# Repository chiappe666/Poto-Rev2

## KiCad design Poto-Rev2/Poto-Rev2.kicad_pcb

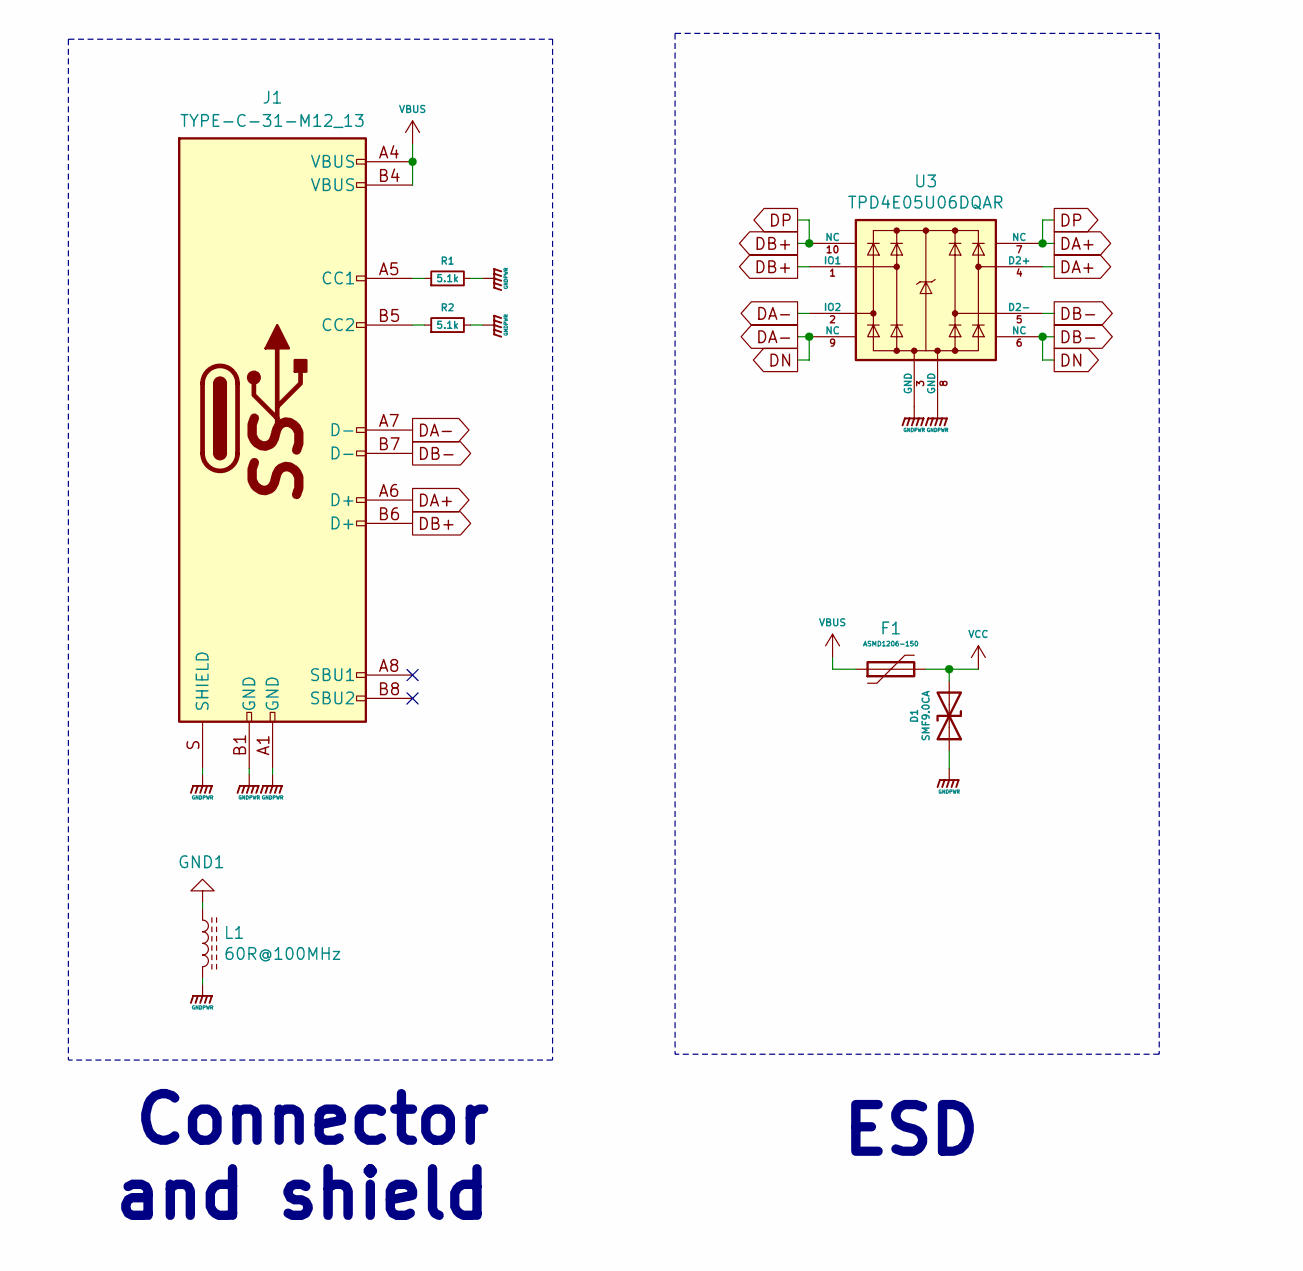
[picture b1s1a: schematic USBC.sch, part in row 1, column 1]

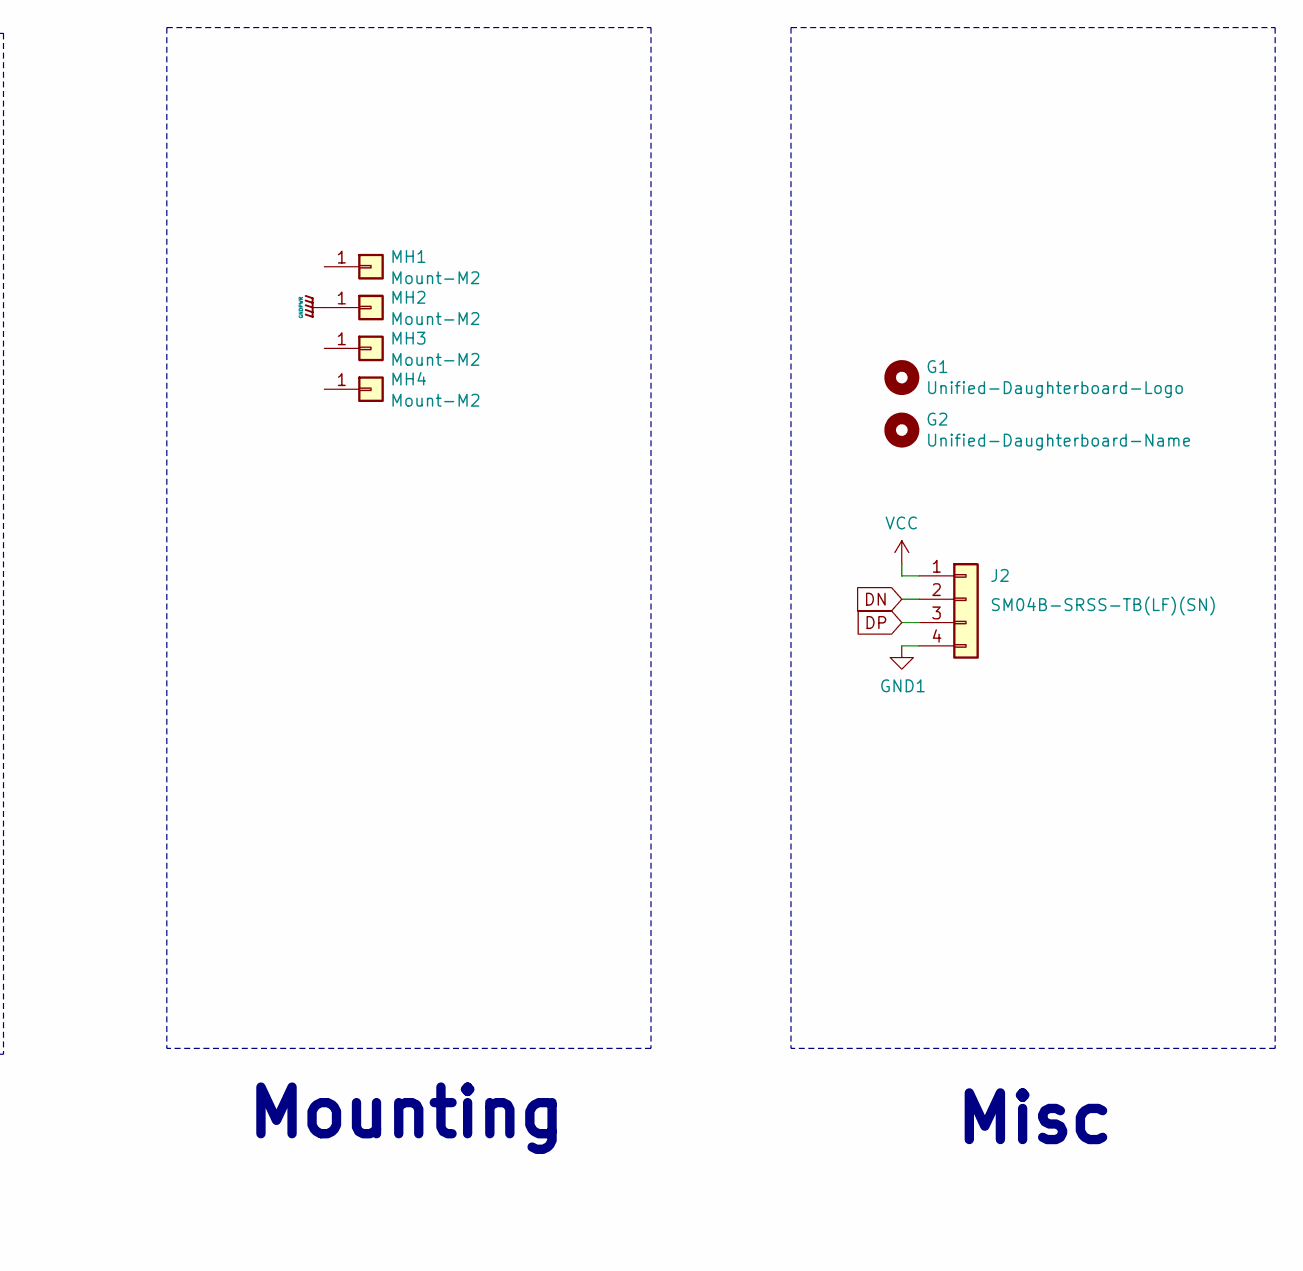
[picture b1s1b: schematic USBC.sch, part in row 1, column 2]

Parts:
D1: SMF9.0CA; D_SOD-123_Bidirectional; Manufacturer Part No SMF9.0CA; LCSC Part No C123799
F1: ASMD1206-150; Fuse_1206_3216Metric; Manufacturer Part No ASMD1206-150; LCSC Part No C135342
G1: Unified-Daughterboard-Logo; Unified-Daughterboard-Logo.pretty
G2: Unified-Daughterboard-Name; Unified-Daughterboard-Name.pretty
J1: TYPE-C-31-M12_13; TYPE-C-31-M-12; Manufacturer Part No TYPE-C-31-M-12; LCSC Part No C165948
J2: SM04B-SRSS-TB(LF)(SN); JST-SR-4; Manufacturer Part No SM04B-SRSS-TB(LF)(SN); LCSC Part No C160404
L1: 60R@100MHz; L_1206_3216Metric; Manufacturer Part No MLB3216-600P4A(f); LCSC Part No C33600
MH1, MH2, MH3, MH4: Mount-M2; Generic-Mounthole
R1, R2: 5.1k; R_0603_1608Metric; LCSC Part No C23186
U1: TPD4E05U06DQAR; USON-10_2.5x1.0mm_P0.5mm; Manufacturer Part No TPD4E05U06DQAR; LCSC Part No C138714

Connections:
GND1: J2.4, L1.1
unnamed: J1.A5 (CC1), R1.1
unnamed: J1.B5 (CC2), R2.1
VBUS: F1.1, J1.A4 (VBUS), J1.B4 (VBUS)
VCC: D1.2 (A2), F1.2, J2.1

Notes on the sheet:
Connector and shield
ESD
Mounting
Misc

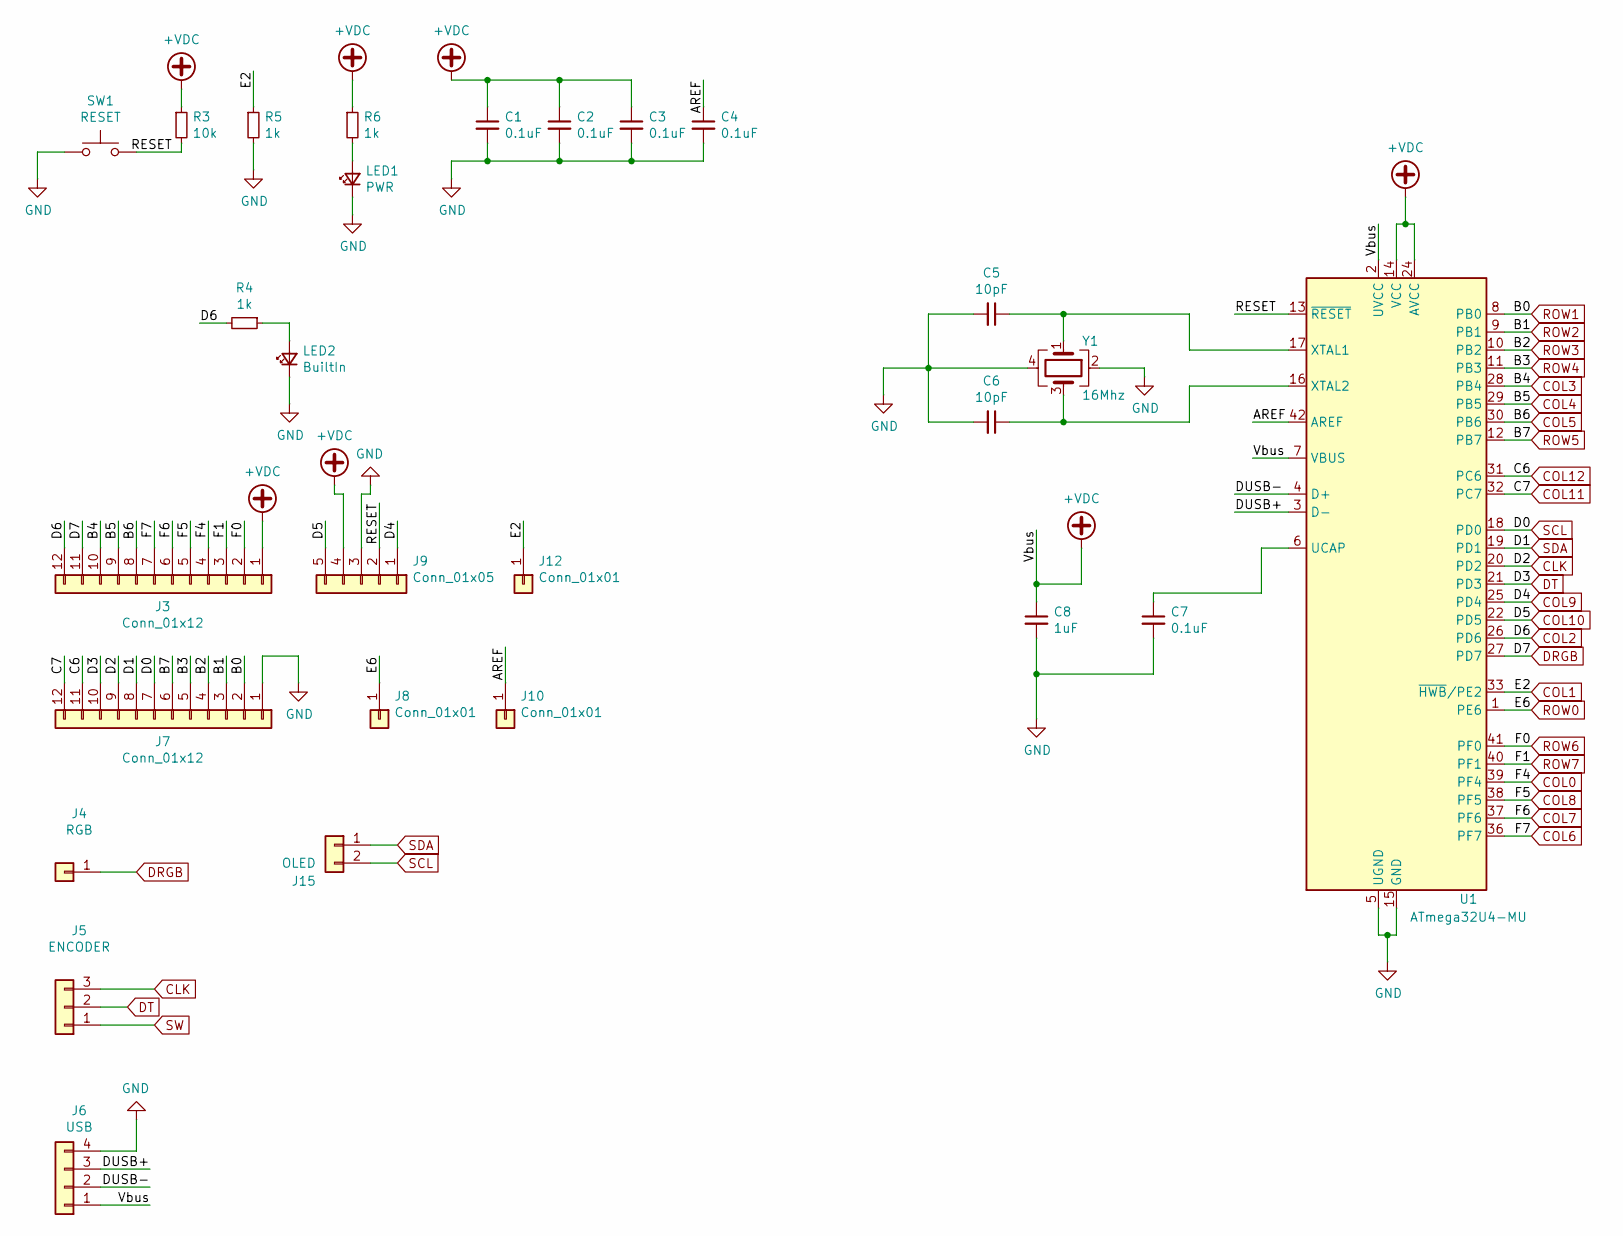
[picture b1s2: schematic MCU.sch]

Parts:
C1, C2, C3, C4, C7: 0.1uF; C_0402_1005Metric_Pad0.74x0.62mm_HandSolder; Manufacturer Part No CL05B104KO5NNNC; LCSC Part No C1525
C5, C6: 10pF; C_0402_1005Metric_Pad0.74x0.62mm_HandSolder; Manufacturer Part No CL05C100JB5NNNC; LCSC Part No C32949
C8: 1uF; C_0402_1005Metric_Pad0.74x0.62mm_HandSolder; Manufacturer Part No CL05A105KA5NQNC; LCSC Part No C52923
J3, J7: Conn_01x12; PinHeader_1x12_P2.54mm_Vertical
J4: RGB; PinHeader_1x01_P2.54mm_Vertical
J5: ENCODER; PinHeader_1x03_P2.54mm_Vertical
J6: USB; JST-SR-4
J8, J10: Conn_01x01; PinHeader_1x01_P2.54mm_Vertical
J9: Conn_01x05; PinHeader_1x05_P2.54mm_Vertical
J12: Conn_01x01; PinHeader_1x01_P1.00mm_Vertical
J15: OLED; PinHeader_1x02_P2.54mm_Vertical
LED1: PWR; LED_0603_1608Metric_Pad1.05x0.95mm_HandSolder
LED2: BuiltIn; LED_0603_1608Metric_Pad1.05x0.95mm_HandSolder
R3: 10k; R_0603_1608Metric_Pad0.98x0.95mm_HandSolder
R4, R5, R6: 1k; R_0603_1608Metric_Pad0.98x0.95mm_HandSolder
SW1: RESET; K2-1187SQ-A4SW-06
U1: ATmega32U4-MU; QFN-44-1EP_7x7mm_P0.5mm_EP5.2x5.2mm
Y1: 16Mhz; Crystal_SMD_3225-4Pin_3.2x2.5mm_HandSoldering

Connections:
/MCU/AREF: C4.1, J10.1, U1.42 (AREF)
/MCU/RESET: J9.2, R3.2, SW1.2, U1.13 (~RESET)
CLK: J5.3, J7.9, U1.20 (PD2)
COL0: J3.4, U1.39 (PF4); also elsewhere on the board
COL1: J12.1, R5.1, U1.33 (~HWB~/PE2); also elsewhere on the board
COL2: J3.12, R4.2, U1.26 (PD6); also elsewhere on the board
COL3: J3.10, U1.28 (PB4); also elsewhere on the board
COL4: J3.9, U1.29 (PB5); also elsewhere on the board
COL5: J3.8, U1.30 (PB6); also elsewhere on the board
COL6: J3.7, U1.36 (PF7); also elsewhere on the board
COL7: J3.6, U1.37 (PF6); also elsewhere on the board
COL8: J3.5, U1.38 (PF5); also elsewhere on the board
COL9: J9.1, U1.25 (PD4); also elsewhere on the board
COL10: J9.5, U1.22 (PD5); also elsewhere on the board
COL11: J7.12, U1.32 (PC7); also elsewhere on the board
COL12: J7.11, U1.31 (PC6); also elsewhere on the board
DRGB: J3.11, J4.1, U1.27 (PD7)
DT: J5.2, J7.10, U1.21 (PD3)
unnamed: C5.1, U1.17 (XTAL1), Y1.1
unnamed: C6.1, U1.16 (XTAL2), Y1.3
unnamed 127: LED1.2 (A), R6.2; also elsewhere on the board
unnamed 128: LED2.2 (A), R4.1; also elsewhere on the board
ROW4: J7.5, U1.11 (PB3); also elsewhere on the board
ROW5: J7.6, U1.12 (PB7); also elsewhere on the board
ROW6: J3.2, U1.41 (PF0); also elsewhere on the board
ROW7: J3.3, U1.40 (PF1); also elsewhere on the board
SCL: J7.7, J15.2, U1.18 (PD0)
SDA: J7.8, J15.1, U1.19 (PD1)
SW: J5.1; also elsewhere on the board

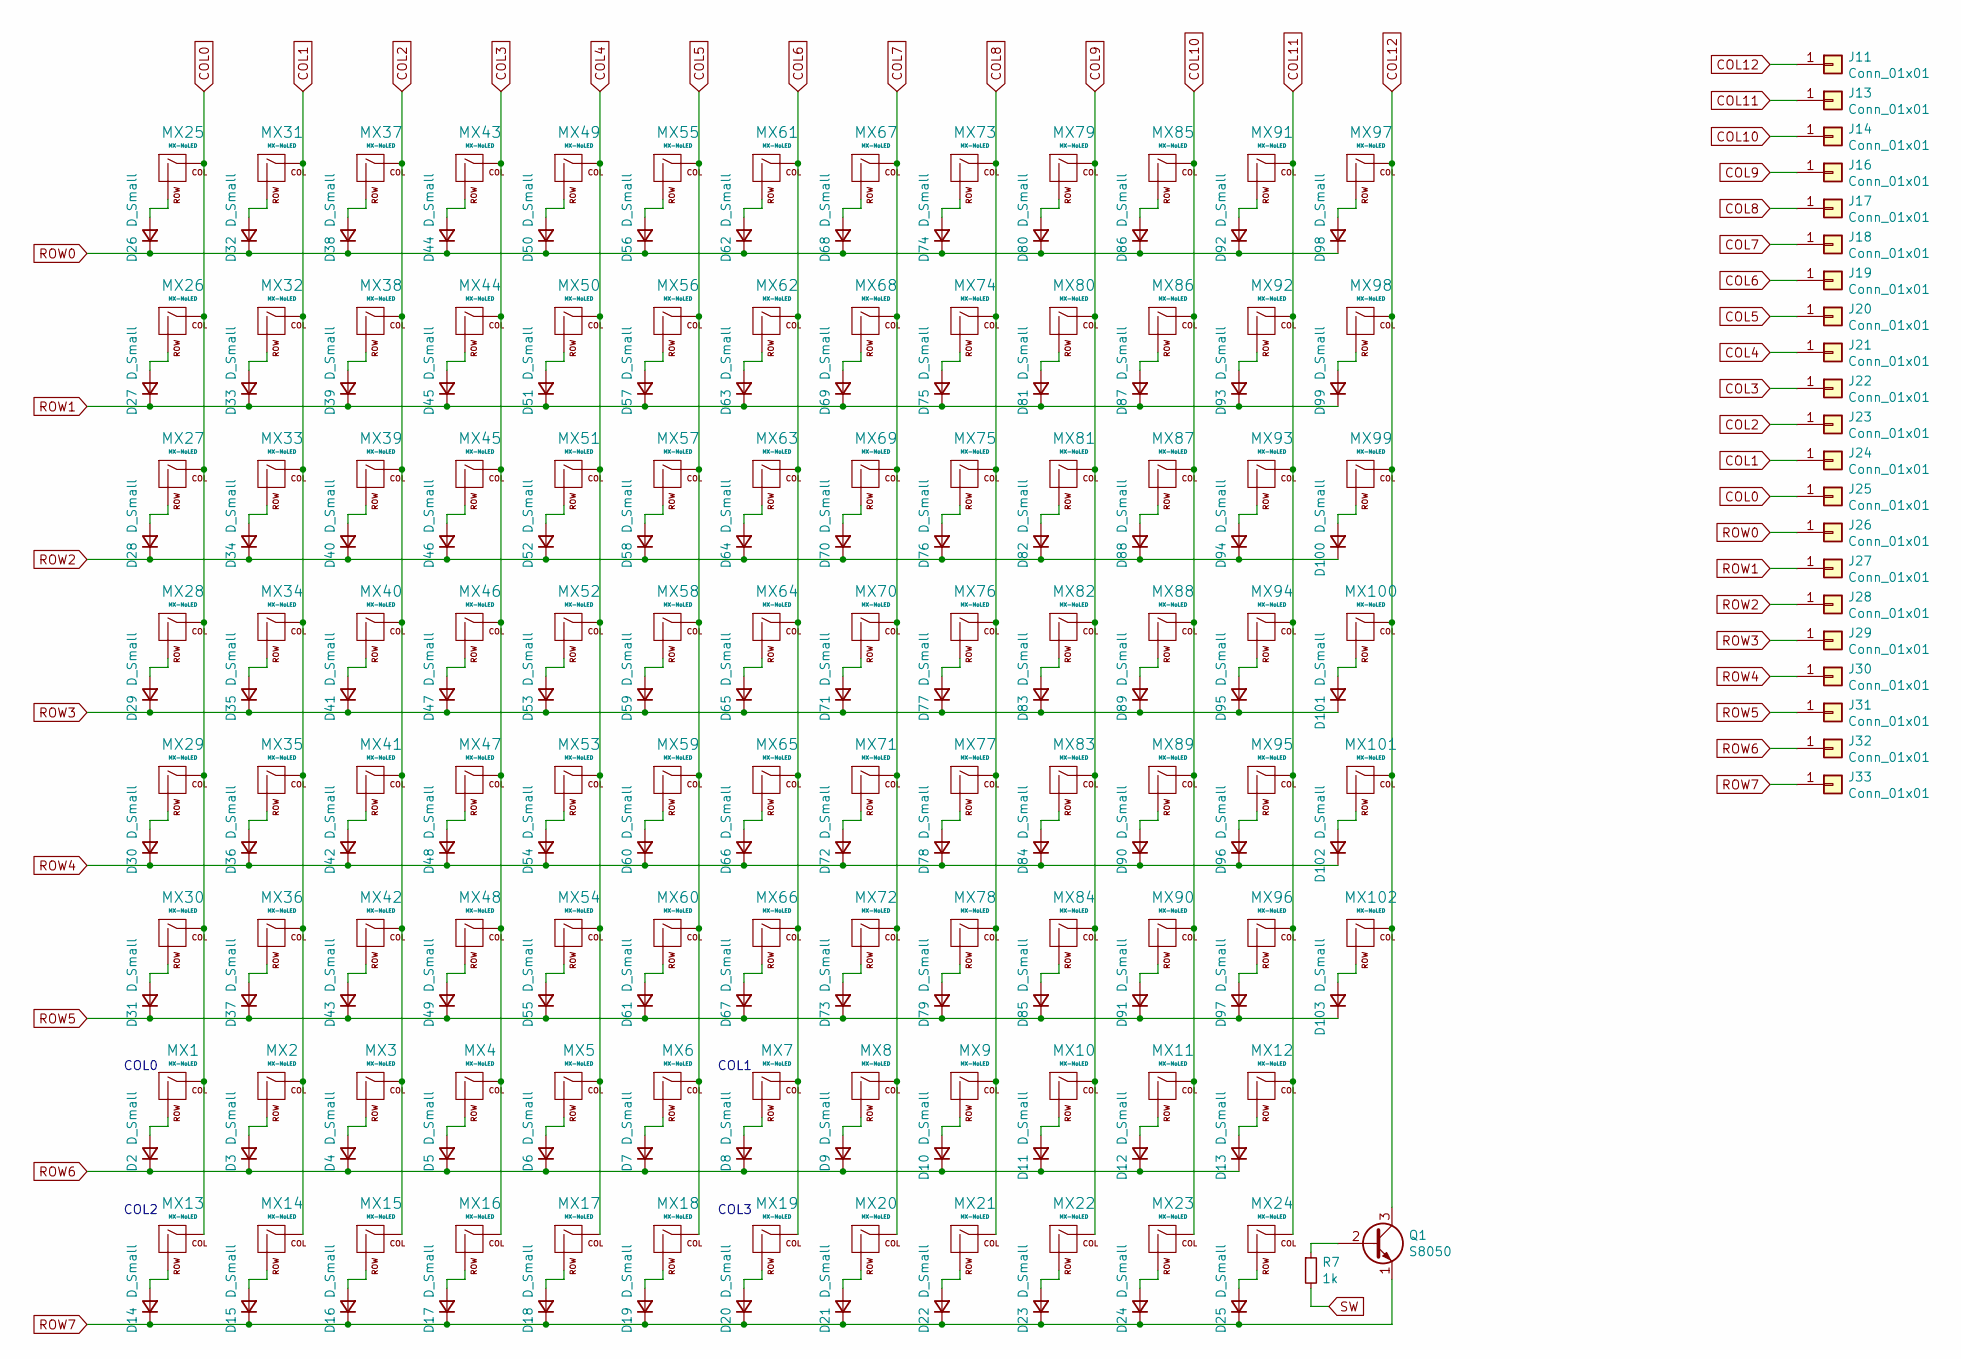
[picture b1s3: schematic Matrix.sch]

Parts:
D2, D3, D4, D5, D6, D7, D8, D9, D10, D11, D12, D13, D14, D15, D16, D17, D18, D19, D20, D21, D22, D23, D24, D25, D26, D27, D28, D29, D30, D31, D32, D33, D34, D35, D36, D37, D38, D39, D40, D41, D42, D43, D44, D45, D46, D47, D48, D49, D50, D51, D52, D53, D54, D55, D56, D57, D58, D59, D60, D61, D62, D63, D64, D65, D66, D67, D68, D69, D70, D71, D72, D73, D74, D75, D76, D77, D78, D79, D80, D81, D82, D83, D84, D85, D86, D87, D88, D89, D90, D91, D92, D93, D94, D95, D96, D97, D98, D99, D100, D101, D102, D103: D_Small; D_SOD-123; LCSC Part No C81598
J11, J13, J14, J16, J17, J18, J19, J20, J21, J22, J23, J24, J25, J26, J27, J28, J29, J30, J31, J32, J33: Conn_01x01; SolderWirePad_1x01_SMD_1x2mm
MX1, MX2, MX3, MX4, MX5, MX6, MX7, MX8, MX9, MX10, MX11, MX12, MX13, MX14, MX15, MX16, MX17, MX18, MX19, MX20, MX21, MX22, MX23, MX24, MX25, MX26, MX27, MX28, MX29, MX30, MX31, MX32, MX33, MX34, MX35, MX36, MX37, MX38, MX39, MX40, MX41, MX42, MX43, MX44, MX45, MX46, MX47, MX48, MX49, MX50, MX51, MX52, MX53, MX54, MX55, MX56, MX57, MX58, MX59, MX60, MX61, MX62, MX63, MX64, MX65, MX66, MX67, MX68, MX69, MX70, MX71, MX72, MX73, MX74, MX75, MX76, MX77, MX78, MX79, MX80, MX81, MX82, MX83, MX84, MX85, MX86, MX87, MX88, MX89, MX90, MX91, MX92, MX93, MX94, MX95, MX96, MX97, MX98, MX99, MX100, MX101, MX102: MX-NoLED; MXOnly-1U-Hotswap-Antishear
Q1: S8050; SOT-23; Manufacturer Part No SS8050; LCSC Part No C2150
R7: 1k; R_0603_1608Metric_Pad0.98x0.95mm_HandSolder; LCSC Part No C21190

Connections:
COL0: J25.1, MX1.1 (COL), MX13.1 (COL), MX25.1 (COL), MX26.1 (COL), MX27.1 (COL), MX28.1 (COL), MX29.1 (COL), MX30.1 (COL); also elsewhere on the board
COL1: J24.1, MX2.1 (COL), MX14.1 (COL), MX31.1 (COL), MX32.1 (COL), MX33.1 (COL), MX34.1 (COL), MX35.1 (COL), MX36.1 (COL); also elsewhere on the board
COL2: J23.1, MX3.1 (COL), MX15.1 (COL), MX37.1 (COL), MX38.1 (COL), MX39.1 (COL), MX40.1 (COL), MX41.1 (COL), MX42.1 (COL); also elsewhere on the board
COL3: J22.1, MX4.1 (COL), MX16.1 (COL), MX43.1 (COL), MX44.1 (COL), MX45.1 (COL), MX46.1 (COL), MX47.1 (COL), MX48.1 (COL); also elsewhere on the board
COL4: J21.1, MX5.1 (COL), MX17.1 (COL), MX49.1 (COL), MX50.1 (COL), MX51.1 (COL), MX52.1 (COL), MX53.1 (COL), MX54.1 (COL); also elsewhere on the board
COL5: J20.1, MX6.1 (COL), MX18.1 (COL), MX55.1 (COL), MX56.1 (COL), MX57.1 (COL), MX58.1 (COL), MX59.1 (COL), MX60.1 (COL); also elsewhere on the board
COL6: J19.1, MX7.1 (COL), MX19.1 (COL), MX61.1 (COL), MX62.1 (COL), MX63.1 (COL), MX64.1 (COL), MX65.1 (COL), MX66.1 (COL); also elsewhere on the board
COL7: J18.1, MX8.1 (COL), MX20.1 (COL), MX67.1 (COL), MX68.1 (COL), MX69.1 (COL), MX70.1 (COL), MX71.1 (COL), MX72.1 (COL); also elsewhere on the board
COL8: J17.1, MX9.1 (COL), MX21.1 (COL), MX73.1 (COL), MX74.1 (COL), MX75.1 (COL), MX76.1 (COL), MX77.1 (COL), MX78.1 (COL); also elsewhere on the board
COL9: J16.1, MX10.1 (COL), MX22.1 (COL), MX79.1 (COL), MX80.1 (COL), MX81.1 (COL), MX82.1 (COL), MX83.1 (COL), MX84.1 (COL); also elsewhere on the board
COL10: J14.1, MX11.1 (COL), MX23.1 (COL), MX85.1 (COL), MX86.1 (COL), MX87.1 (COL), MX88.1 (COL), MX89.1 (COL), MX90.1 (COL); also elsewhere on the board
COL11: J13.1, MX12.1 (COL), MX24.1 (COL), MX91.1 (COL), MX92.1 (COL), MX93.1 (COL), MX94.1 (COL), MX95.1 (COL), MX96.1 (COL); also elsewhere on the board
COL12: J11.1, MX97.1 (COL), MX98.1 (COL), MX99.1 (COL), MX100.1 (COL), MX101.1 (COL), MX102.1 (COL), Q1.3 (C); also elsewhere on the board
unnamed: D2.2 (A), MX1.2 (ROW)
unnamed: D3.2 (A), MX2.2 (ROW)
unnamed: D4.2 (A), MX3.2 (ROW)
unnamed: D5.2 (A), MX4.2 (ROW)
unnamed: D6.2 (A), MX5.2 (ROW)
unnamed: D7.2 (A), MX6.2 (ROW)
unnamed: D8.2 (A), MX7.2 (ROW)
unnamed: D9.2 (A), MX8.2 (ROW)
unnamed: D10.2 (A), MX9.2 (ROW)
unnamed: D11.2 (A), MX10.2 (ROW)
unnamed: D12.2 (A), MX11.2 (ROW)
unnamed: D13.2 (A), MX12.2 (ROW)
unnamed: D14.2 (A), MX13.2 (ROW)
unnamed: D15.2 (A), MX14.2 (ROW)
unnamed: D16.2 (A), MX15.2 (ROW)
unnamed: D17.2 (A), MX16.2 (ROW)
unnamed: D18.2 (A), MX17.2 (ROW)
unnamed: D19.2 (A), MX18.2 (ROW)
unnamed: D20.2 (A), MX19.2 (ROW)
unnamed: D21.2 (A), MX20.2 (ROW)
unnamed: D22.2 (A), MX21.2 (ROW)
unnamed: D23.2 (A), MX22.2 (ROW)
unnamed: D24.2 (A), MX23.2 (ROW)
unnamed: D25.2 (A), MX24.2 (ROW)
unnamed: D26.2 (A), MX25.2 (ROW)
unnamed: D27.2 (A), MX26.2 (ROW)
unnamed: D28.2 (A), MX27.2 (ROW)
unnamed: D29.2 (A), MX28.2 (ROW)
unnamed: D30.2 (A), MX29.2 (ROW)
unnamed: D31.2 (A), MX30.2 (ROW)
unnamed: D32.2 (A), MX31.2 (ROW)
unnamed: D33.2 (A), MX32.2 (ROW)
unnamed: D34.2 (A), MX33.2 (ROW)
unnamed: D35.2 (A), MX34.2 (ROW)
unnamed: D36.2 (A), MX35.2 (ROW)
unnamed: D37.2 (A), MX36.2 (ROW)
unnamed: D38.2 (A), MX37.2 (ROW)
unnamed: D39.2 (A), MX38.2 (ROW)
unnamed: D40.2 (A), MX39.2 (ROW)
unnamed: D41.2 (A), MX40.2 (ROW)
unnamed: D42.2 (A), MX41.2 (ROW)
unnamed: D43.2 (A), MX42.2 (ROW)
unnamed: D44.2 (A), MX43.2 (ROW)
unnamed: D45.2 (A), MX44.2 (ROW)
unnamed: D46.2 (A), MX45.2 (ROW)
unnamed: D47.2 (A), MX46.2 (ROW)
unnamed: D48.2 (A), MX47.2 (ROW)
unnamed: D49.2 (A), MX48.2 (ROW)
unnamed: D50.2 (A), MX49.2 (ROW)
unnamed: D51.2 (A), MX50.2 (ROW)
unnamed: D52.2 (A), MX51.2 (ROW)
unnamed: D53.2 (A), MX52.2 (ROW)
unnamed: D54.2 (A), MX53.2 (ROW)
unnamed: D55.2 (A), MX54.2 (ROW)
unnamed: D56.2 (A), MX55.2 (ROW)
unnamed: D57.2 (A), MX56.2 (ROW)
unnamed: D58.2 (A), MX57.2 (ROW)
unnamed: D59.2 (A), MX58.2 (ROW)
unnamed: D60.2 (A), MX59.2 (ROW)
unnamed: D61.2 (A), MX60.2 (ROW)
unnamed: D62.2 (A), MX61.2 (ROW)
unnamed: D63.2 (A), MX62.2 (ROW)
unnamed: D64.2 (A), MX63.2 (ROW)
unnamed: D65.2 (A), MX64.2 (ROW)
unnamed: D66.2 (A), MX65.2 (ROW)
unnamed: D67.2 (A), MX66.2 (ROW)
unnamed: D68.2 (A), MX67.2 (ROW)
unnamed: D69.2 (A), MX68.2 (ROW)
unnamed: D70.2 (A), MX69.2 (ROW)
unnamed: D71.2 (A), MX70.2 (ROW)
unnamed: D72.2 (A), MX71.2 (ROW)
unnamed: D73.2 (A), MX72.2 (ROW)
unnamed: D74.2 (A), MX73.2 (ROW)
unnamed: D75.2 (A), MX74.2 (ROW)
unnamed: D76.2 (A), MX75.2 (ROW)
unnamed: D77.2 (A), MX76.2 (ROW)
unnamed: D78.2 (A), MX77.2 (ROW)
unnamed: D79.2 (A), MX78.2 (ROW)
unnamed: D80.2 (A), MX79.2 (ROW)
unnamed: D81.2 (A), MX80.2 (ROW)
unnamed: D82.2 (A), MX81.2 (ROW)
unnamed: D83.2 (A), MX82.2 (ROW)
unnamed: D84.2 (A), MX83.2 (ROW)
unnamed: D85.2 (A), MX84.2 (ROW)
unnamed: D86.2 (A), MX85.2 (ROW)
unnamed: D87.2 (A), MX86.2 (ROW)
unnamed: D88.2 (A), MX87.2 (ROW)
unnamed: D89.2 (A), MX88.2 (ROW)
unnamed: D90.2 (A), MX89.2 (ROW)
unnamed: D91.2 (A), MX90.2 (ROW)
unnamed: D92.2 (A), MX91.2 (ROW)
unnamed: D93.2 (A), MX92.2 (ROW)
unnamed: D94.2 (A), MX93.2 (ROW)
unnamed: D95.2 (A), MX94.2 (ROW)
unnamed: D96.2 (A), MX95.2 (ROW)
unnamed: D97.2 (A), MX96.2 (ROW)
unnamed: D98.2 (A), MX97.2 (ROW)
unnamed: D99.2 (A), MX98.2 (ROW)
unnamed: D100.2 (A), MX99.2 (ROW)
unnamed: D101.2 (A), MX100.2 (ROW)
unnamed: D102.2 (A), MX101.2 (ROW)
unnamed: D103.2 (A), MX102.2 (ROW)
unnamed: Q1.2 (B), R7.1
ROW4: D30.1 (K), D36.1 (K), D42.1 (K), D48.1 (K), D54.1 (K), D60.1 (K), D66.1 (K), D72.1 (K), D78.1 (K), D84.1 (K), D90.1 (K), D96.1 (K), D102.1 (K), J30.1; also elsewhere on the board
ROW5: D31.1 (K), D37.1 (K), D43.1 (K), D49.1 (K), D55.1 (K), D61.1 (K), D67.1 (K), D73.1 (K), D79.1 (K), D85.1 (K), D91.1 (K), D97.1 (K), D103.1 (K), J31.1; also elsewhere on the board
ROW6: D2.1 (K), D3.1 (K), D4.1 (K), D5.1 (K), D6.1 (K), D7.1 (K), D8.1 (K), D9.1 (K), D10.1 (K), D11.1 (K), D12.1 (K), D13.1 (K), J32.1; also elsewhere on the board
ROW7: D14.1 (K), D15.1 (K), D16.1 (K), D17.1 (K), D18.1 (K), D19.1 (K), D20.1 (K), D21.1 (K), D22.1 (K), D23.1 (K), D24.1 (K), D25.1 (K), J33.1, Q1.1 (E); also elsewhere on the board
SW: R7.2; also elsewhere on the board

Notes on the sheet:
COL0
COL1
COL2
COL3

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
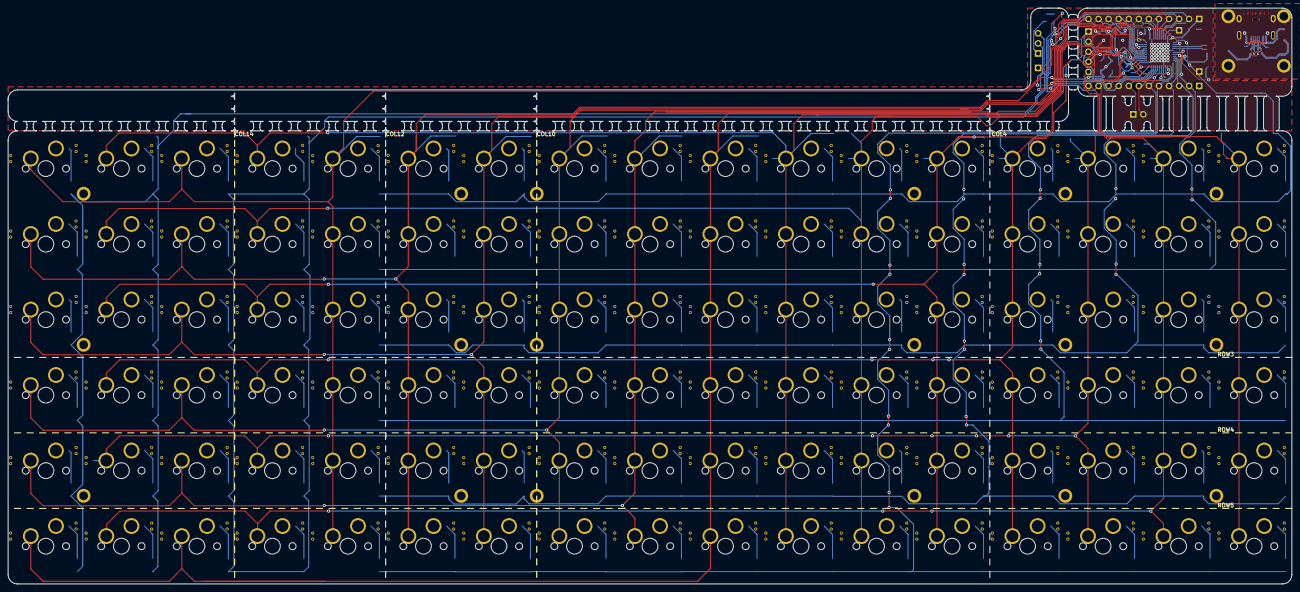
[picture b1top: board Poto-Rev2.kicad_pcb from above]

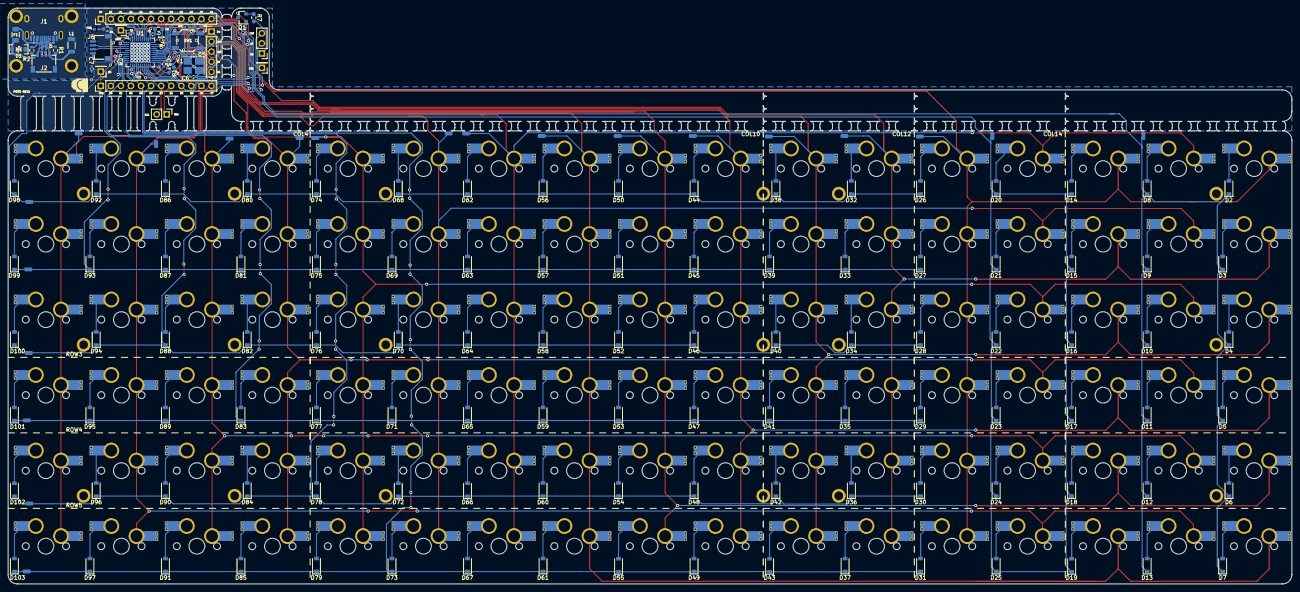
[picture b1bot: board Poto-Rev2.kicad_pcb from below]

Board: 2 copper layers, 323.9 x 145.3 mm, 268 parts (164 on the bottom side), 149 nets.

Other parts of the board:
LED: BuiltIn; LED_0402_1005Metric_Pad0.77x0.64mm_HandSolder
PWR: PWR; LED_0402_1005Metric_Pad0.77x0.64mm_HandSolder
U3: TPD4E05U06DQAR; USON-10_2.5x1.0mm_P0.5mm

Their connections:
unnamed 127: PWR.2; also elsewhere on the board
unnamed 128: LED.2; also elsewhere on the board

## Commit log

2021-10-02 Add submodules
2021-10-02 preparing libraries and adding submodule
2021-10-02 deleting submodule
2021-10-02 moved libraries folder
2021-10-03 adding submodule
2021-10-03 removing submodules
2021-10-03 remove submodule files
2021-10-03 stuff
2021-10-03 moved submodules folder
    moved submodules to libraries folder
2021-10-03 fixing libraries and setting up stuff
2021-12-06 Big Chungus Update
    Almost Everything Done
2021-12-08 added some pads
    added some pads for columns and rows
2021-12-11 uwu
    awa
